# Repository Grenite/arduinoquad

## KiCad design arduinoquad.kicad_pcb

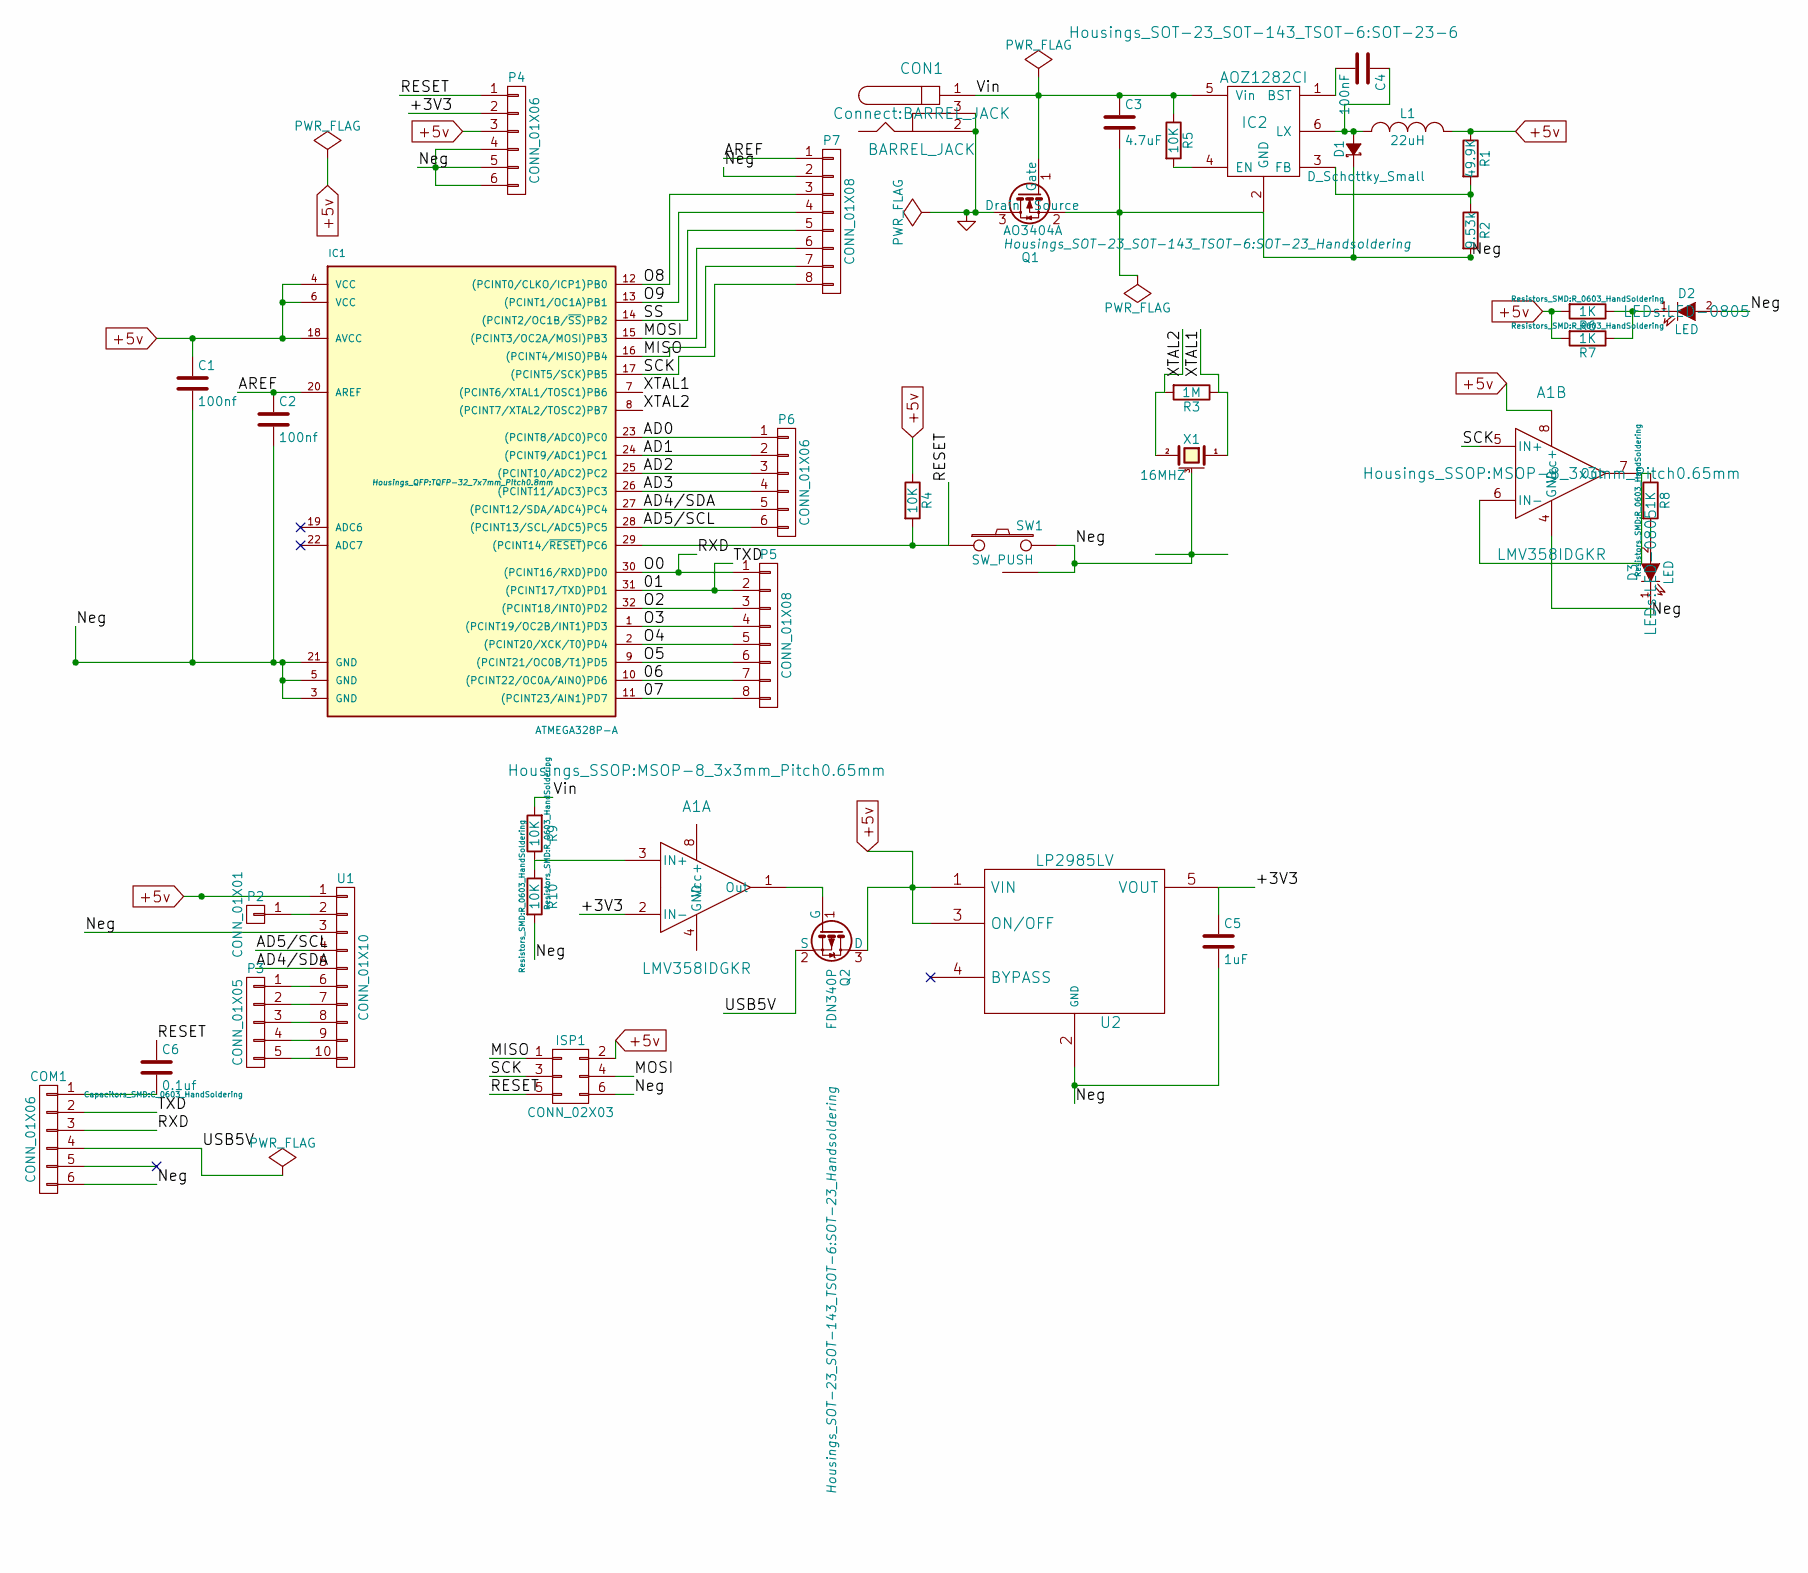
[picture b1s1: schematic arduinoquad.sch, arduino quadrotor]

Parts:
A1: LMV358IDGKR; MSOP-8_3x3mm_Pitch0.65mm
C1, C2: 100nf; C_0603_HandSoldering
C3: 4.7uF; C_0603_HandSoldering
C4: 100nF; C_0603_HandSoldering
C5: 1uF; C_0603_HandSoldering
C6: 0.1uf; C_0603_HandSoldering
COM1: CONN_01X06; Socket_Strip_Angled_1x06
CON1: BARREL_JACK
D1: D_Schottky_Small; Diode-SMB_Handsoldering
D2, D3: LED; LED-0805
IC1: ATMEGA328P-A; TQFP-32_7x7mm_Pitch0.8mm
IC2: AOZ1282CI; SOT-23-6
ISP1: CONN_02X03; Pin_Header_Straight_2x03
L1: 22uH; WE-PD_SMD_Shielded_Power_Inductor
P2: CONN_01X01; Pin_Header_Straight_1x01
P3: CONN_01X05; Pin_Header_Straight_1x05
P4, P6: CONN_01X06; Pin_Header_Straight_1x06
P5, P7: CONN_01X08; Pin_Header_Straight_1x08
Q1: AO3404A; SOT-23_Handsoldering
Q2: FDN340P; SOT-23_Handsoldering
R1: 49.9K; R_0805_HandSoldering
R2: 9.53k; R_0805_HandSoldering
R3: 1M; R_0805_HandSoldering
R4, R5: 10K; R_0805_HandSoldering
R6, R7, R8: 1K; R_0603_HandSoldering
R9, R10: 10K; R_0603_HandSoldering
SW1: SW_PUSH; SW_SPST_FSM1LP
U1: CONN_01X10; Pin_Header_Straight_1x10
U2: LP2985LV; SOT-23-5
X1: 16MHZ; CSTCE_V

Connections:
+5v: A1.8 (Vcc+), C1.1, IC1.4 (VCC), IC1.6 (VCC), IC1.18 (AVCC), ISP1.2, L1.2, P4.3, Q2.3 (D), R1.1, R4.1, R6.2, R7.2, U1.1, U2.1 (VIN), U2.3 (ON/OFF)
/01: COM1.2, IC1.31 ((PCINT17/TXD)PD1), P5.2
/06: IC1.10 ((PCINT22/OC0A/AIN0)PD6), P5.7
/07: IC1.11 ((PCINT23/AIN1)PD7), P5.8
/+3V3: A1.2 (IN-), C5.1, P4.2, U2.5 (VOUT)
/AD0: IC1.23 ((PCINT8/ADC0)PC0), P6.1
/AD1: IC1.24 ((PCINT9/ADC1)PC1), P6.2
/AD2: IC1.25 ((PCINT10/ADC2)PC2), P6.3
/AD3: IC1.26 ((PCINT11/ADC3)PC3), P6.4
/AD4/SDA: IC1.27 ((PCINT12/SDA/ADC4)PC4), P6.5, U1.5
/AD5/SCL: IC1.28 ((PCINT13/SCL/ADC5)PC5), P6.6, U1.4
/AREF: C2.1, IC1.20 (AREF), P7.1
/MISO: IC1.16 ((PCINT4/MISO)PB4), ISP1.1, P7.7
/MOSI: IC1.15 ((PCINT3/OC2A/MOSI)PB3), ISP1.4, P7.6
/Neg: A1.4 (GND), C1.2, C2.2, C3.2, C5.2, COM1.6, D1.1 (K), D2.2 (A), D3.1 (K), IC1.3 (GND), IC1.5 (GND), IC1.21 (GND), IC2.2 (GND), ISP1.6, P4.4, P4.5, P4.6, P7.2, Q1.2 (Source), R2.2, R10.2, SW1.2, SW1.3 (GND), U1.3, U2.2 (GND), X1.3 (case)
/O0: COM1.3, IC1.30 ((PCINT16/RXD)PD0), P5.1
/O2: IC1.32 ((PCINT18/INT0)PD2), P5.3
/O3: IC1.1 ((PCINT19/OC2B/INT1)PD3), P5.4
/O4: IC1.2 ((PCINT20/XCK/T0)PD4), P5.5
/O5: IC1.9 ((PCINT21/OC0B/T1)PD5), P5.6
/O8: IC1.12 ((PCINT0/CLKO/ICP1)PB0), P7.3
/O9: IC1.13 ((PCINT1/OC1A)PB1), P7.4
/RESET: C6.1, IC1.29 ((PCINT14/~RESET~)PC6), ISP1.5, P4.1, R4.2, SW1.1
/SCK: A1.5 (IN+), IC1.17 ((PCINT5/SCK)PB5), ISP1.3, P7.8
/SS: IC1.14 ((PCINT2/OC1B/~SS~)PB2), P7.5
/USB5V: COM1.4, Q2.2 (S)
/Vin: C3.1, CON1.1, IC2.5 (Vin), Q1.1 (Gate), R5.1, R9.2
/XTAL1: IC1.7 ((PCINT6/XTAL1/TOSC1)PB6), R3.1, X1.1
/XTAL2: IC1.8 ((PCINT7/XTAL2/TOSC2)PB7), R3.2, X1.2
GND: CON1.2, CON1.3, Q1.3 (Drain)
unnamed: A1.1 (Out), Q2.1 (G)
unnamed: A1.3 (IN+), R9.1, R10.1
unnamed: A1.6 (IN-), A1.7 (Out), R8.1
unnamed: C4.1, D1.2 (A), IC2.6 (LX), L1.1
unnamed: C4.2, IC2.1 (BST)
unnamed: C6.2, COM1.1
unnamed: D2.1 (K), R6.1, R7.1
unnamed: D3.2 (A), R8.2
unnamed: IC2.3 (FB), R1.2, R2.1
unnamed: IC2.4 (EN), R5.2
unnamed 43: P2.1, U1.2; also elsewhere on the board
unnamed: P3.1, U1.6
unnamed: P3.2, U1.7
unnamed: P3.3, U1.8
unnamed: P3.4, U1.9
unnamed: P3.5, U1.10

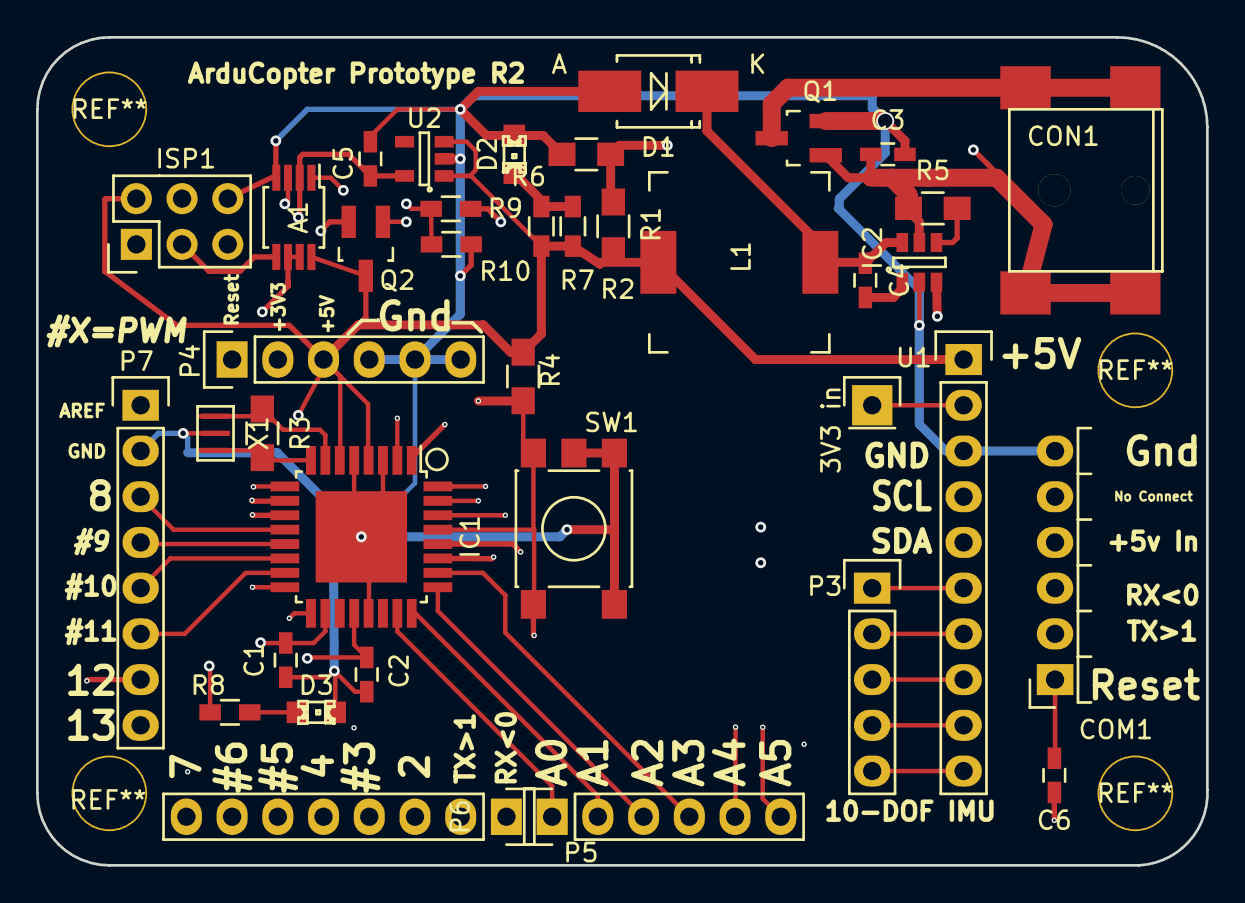
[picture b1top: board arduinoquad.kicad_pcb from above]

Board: 4 copper layers, 65.0 x 46.0 mm, 38 parts (0 on the bottom side), 46 nets.

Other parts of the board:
3V3 in: CONN_01X01; Pin_Header_Straight_1x01

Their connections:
unnamed 43: 3V3 in.1; also elsewhere on the board

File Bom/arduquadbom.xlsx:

Ref | Description | Digikey
C1 | 100 nf cer cap 0603 | 490-1524-2-ND
C2 | 100 nf cer cap 0603 | 490-1524-2-ND
C3 | 4.7 uF cer cap 0603 | 1276-1900-1-ND
C4 | 100nf cer cap 0603 | 490-1524-2-ND
C5 | 1uf cer cap 0603 | 490-3897-1-ND
COM1 | angled male connector 1x6 | 609-3313-ND
CON1 | smd barrel jack 2.1x5.5mm | CP-002AHPJCT-ND
D1 | schottky diode | SL22-E3/52TGICT-ND
D2 | green led 0805 | 475-1410-1-ND
DS1 | 1x5 straight female header | S7038-ND
IC1 | atmega 328p tqfp32 | ATMEGA328P-AURCT-ND
IC2 | AOZ1282CI Switching converter | 785-1613-1-ND
L1 | 22uH inductor shielded | 732-2992-1-ND
P1 | Female header 1x1
P2 | Female header 1x1
P3 | Female header 1x5 | S7038-ND
P4 | female header 1x6 | S7039-ND
P5 | female header 1x8 | S7041-ND
P6 | female header 1x6 | S7039-ND
P7 | female header 1x8 | S7041-ND
Q1 | AO3404A N-Channel MOSFET | 785-1004-1-ND
R1 | 49.9k 0805 res | P49.9KDACT-ND
R2 | 15.8k 0805 res | P15.8KDACT-ND
R3 | 1M 0805 res | P1.00MCCT-ND
R4 | 10k 0805 res | RMCF0805FT10K0CT-ND
R5 | 10k 0805 res | RMCF0805FT10K0CT-ND
R6 | 1k 0603 res | P1.00KHCT-ND
R7 | 1k 0603 res | P1.00KHCT-ND
SW1 | FSM1LP smd tactile pushbutton switch | 450-1760-2-ND
U1 | Female 1x10 header | S7008-ND
U2 | 3.3V regulator SOT-23-5 | 296-18476-1-ND
X1 | 16mHZ Cer resonator | 490-1198-1-ND

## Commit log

2017-01-01 :circus_tent: Added .gitattributes & .gitignore files
